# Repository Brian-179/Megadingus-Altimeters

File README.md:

# Megadingus-Altimeters
Megadingus Altimeters/Dual deploy computers
EVERYTHING HERE IS HIGHLY EXPERIMENTAL AND MOSTLY UNTESTED (for now)

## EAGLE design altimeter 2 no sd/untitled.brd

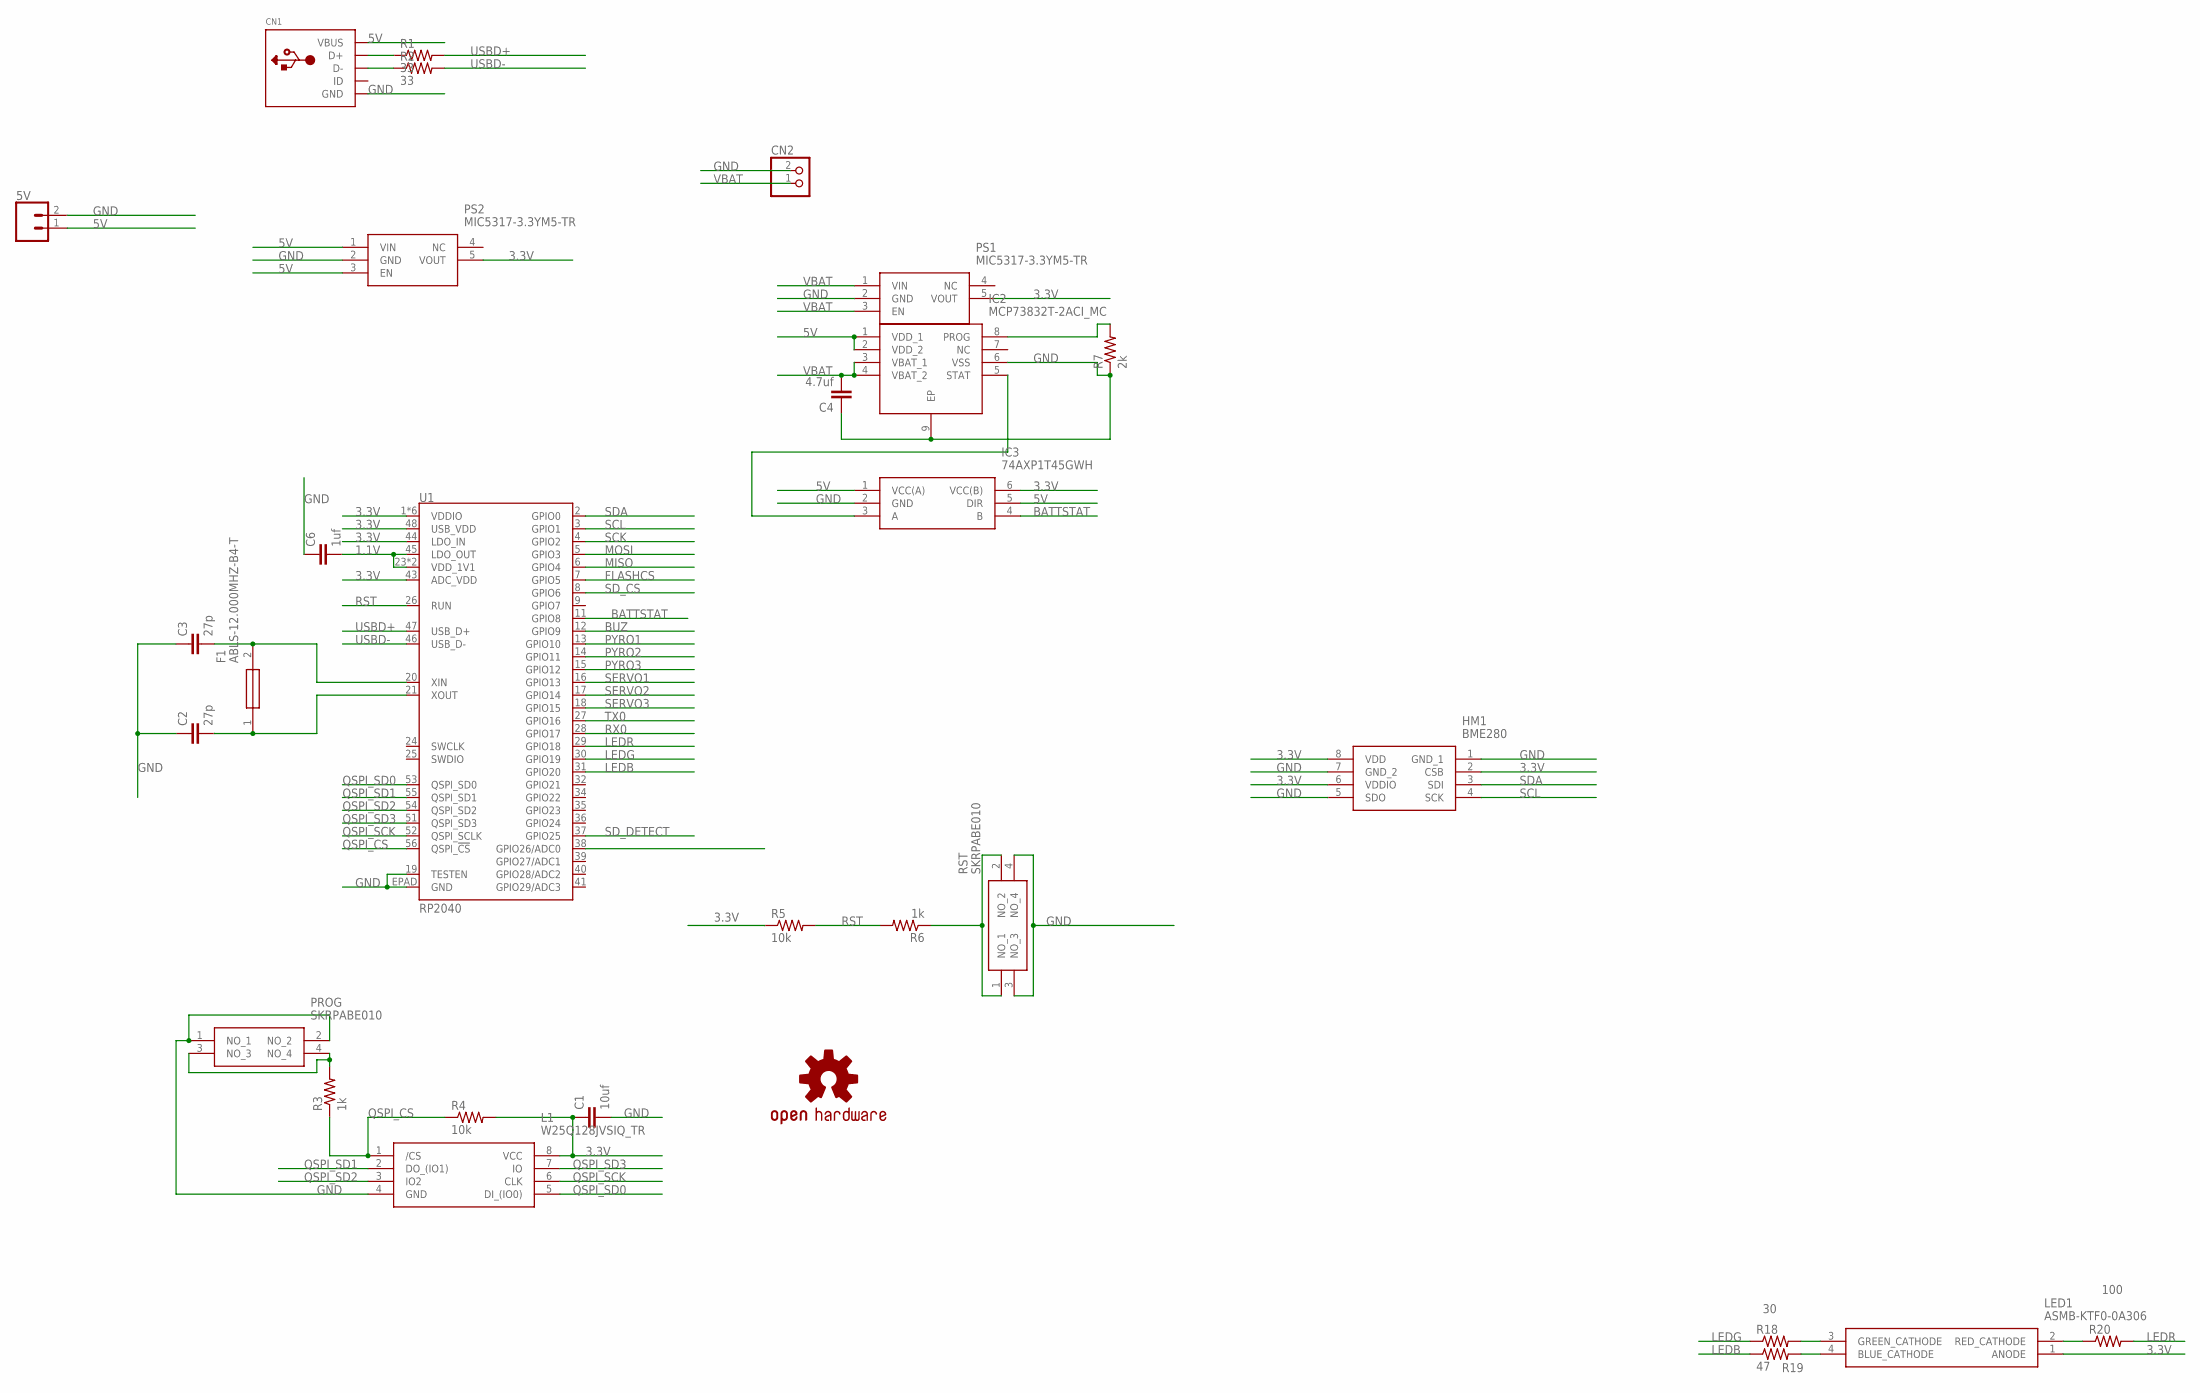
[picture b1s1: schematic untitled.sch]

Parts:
5V: CONN_02; 1X02
C1: 10uf; C0805
C2, C3: 27p; C0805
C4: 4.7uf; C0805
C6: 1uf; C0805
CN1: USBMINIB; USB-MINIB
CN2: JST_2PIN-SMT-RA; JST-PH-2-SMT-RA
F1: ABLS-12.000MHZ-B4-T; HC/49US-(AT49)_1
HM1: BME280
IC2: MCP73832T-2ACI_MC; SON50P300X200X100-9N
IC3: 74AXP1T45GWH
L1: W25Q128JVSIQ_TR; SOIC127P780X195-8N
LED1: ASMB-KTF0-0A306; ASMBKTF00A306
LOGO1: OSHW-LOGOS; OSHW-LOGO-S
PROG: SKRPABE010
PS1, PS2: MIC5317-3.3YM5-TR; SOT95P280X145-5N
R1, R2: 33; M0805
R3, R6: 1k; M0805
R4, R5: 10k; M0805
R7: 2k; M0805
R18: 30; M0805
R19: 47; M0805
R20: 100; M0805
RST: SKRPABE010
U1: RP2040; QFN-56

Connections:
1.1V: C6.2, U1.23 (VDD_1V1), U1.45 (LDO_OUT), U1.50 (VDD_1V1)
3.3V: C1.1, HM1.2 (CSB), HM1.6 (VDDIO), HM1.8 (VDD), IC3.6 (VCC(B)), L1.8 (VCC), LED1.1 (ANODE), PS1.5 (VOUT), PS2.5 (VOUT), R4.2, R5.1, U1.1 (VDDIO), U1.10 (VDDIO), U1.22 (VDDIO), U1.33 (VDDIO), U1.42 (VDDIO), U1.43 (ADC_VDD), U1.44 (LDO_IN), U1.48 (USB_VDD), U1.49 (VDDIO)
5V: 5V.1, CN1.VBUS, IC2.1 (VDD_1), IC2.2 (VDD_2), IC3.1 (VCC(A)), IC3.5 (DIR), PS2.1 (VIN), PS2.3 (EN)
BATTSTAT: IC3.4 (B), U1.11 (GPIO8)
BUZ: U1.12 (GPIO9)
FLASHCS: U1.7 (GPIO5)
GND: 5V.2, C1.2, C2.1, C3.1, C4.1, C6.1, CN1.GND, CN2.2 (1), HM1.1 (GND_1), HM1.5 (SDO), HM1.7 (GND_2), IC2.6 (VSS), IC2.9 (EP), IC3.2 (GND), L1.4 (GND), PROG.1 (NO_1), PROG.2 (NO_2), PS1.2 (GND), PS2.2 (GND), R7.1, RST.3 (NO_3), RST.4 (NO_4), U1.19 (TESTEN), U1.EPAD (GND)
LEDB: R19.1, U1.31 (GPIO20)
LEDG: R18.1, U1.30 (GPIO19)
LEDR: R20.2, U1.29 (GPIO18)
MISO: U1.6 (GPIO4)
MOSI: U1.5 (GPIO3)
unnamed: IC2.8 (PROG), R7.2
unnamed: PROG.3 (NO_3), PROG.4 (NO_4), R3.2
unnamed: IC2.5 (STAT), IC3.3 (A)
unnamed: R6.1, RST.1 (NO_1), RST.2 (NO_2)
unnamed: CN1.D+, R1.1
unnamed: CN1.D-, R2.1
unnamed: C3.2, F1.2, U1.20 (XIN)
unnamed: C2.2, F1.1, U1.21 (XOUT)
unnamed: LED1.3 (GREEN_CATHODE), R18.2
unnamed: LED1.4 (BLUE_CATHODE), R19.2
unnamed: LED1.2 (RED_CATHODE), R20.1
PYRO1: U1.13 (GPIO10)
PYRO2: U1.14 (GPIO11)
PYRO3: U1.15 (GPIO12)
QSPI_CS: L1.1 (/CS), R3.1, R4.1, U1.56 (QSPI_!CS!)
QSPI_SCK: L1.6 (CLK), U1.52 (QSPI_SCLK)
QSPI_SD0: L1.5 (DI_(IO0)), U1.53 (QSPI_SD0)
QSPI_SD1: L1.2 (DO_(IO1)), U1.55 (QSPI_SD1)
QSPI_SD2: L1.3 (IO2), U1.54 (QSPI_SD2)
QSPI_SD3: L1.7 (IO), U1.51 (QSPI_SD3)
RST: R5.2, R6.2, U1.26 (RUN)
RX0: U1.28 (GPIO17)
SCK: U1.4 (GPIO2)
SCL: HM1.4 (SCK), U1.3 (GPIO1)
SDA: HM1.3 (SDI), U1.2 (GPIO0)
SD_CS: U1.8 (GPIO6)
SD_DETECT: U1.37 (GPIO25)
SERVO1: U1.16 (GPIO13)
SERVO2: U1.17 (GPIO14)
SERVO3: U1.18 (GPIO15)
TX0: U1.27 (GPIO16)
USBD+: R1.2, U1.47 (USB_D+)
USBD-: R2.2, U1.46 (USB_D-)
VBAT: C4.2, CN2.1 (2), IC2.3 (VBAT_1), IC2.4 (VBAT_2), PS1.1 (VIN), PS1.3 (EN)

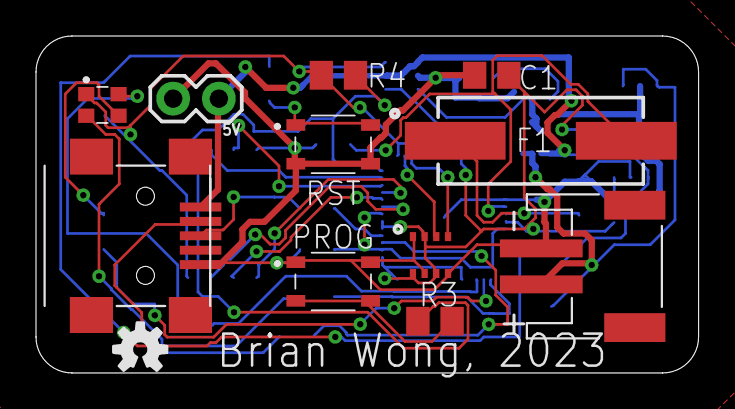
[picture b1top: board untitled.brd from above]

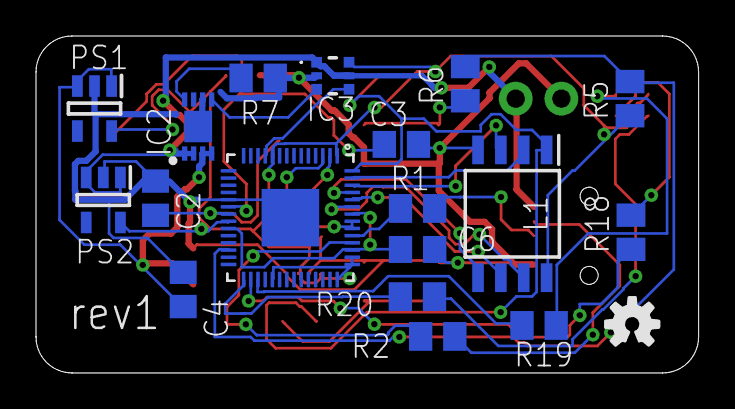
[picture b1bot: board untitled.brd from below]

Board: 2 copper layers, 36.8 x 18.7 mm, 31 parts (19 on the bottom side), 31 nets.

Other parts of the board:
LOGO2: OSHW-LOGOS; OSHW-LOGO-S

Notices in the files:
parts and their libraries:
SparkFun-Connectors: Licensing: Creative Commons ShareAlike 4.0 International - https://creativecommons.org/licenses/by-sa/4.0
